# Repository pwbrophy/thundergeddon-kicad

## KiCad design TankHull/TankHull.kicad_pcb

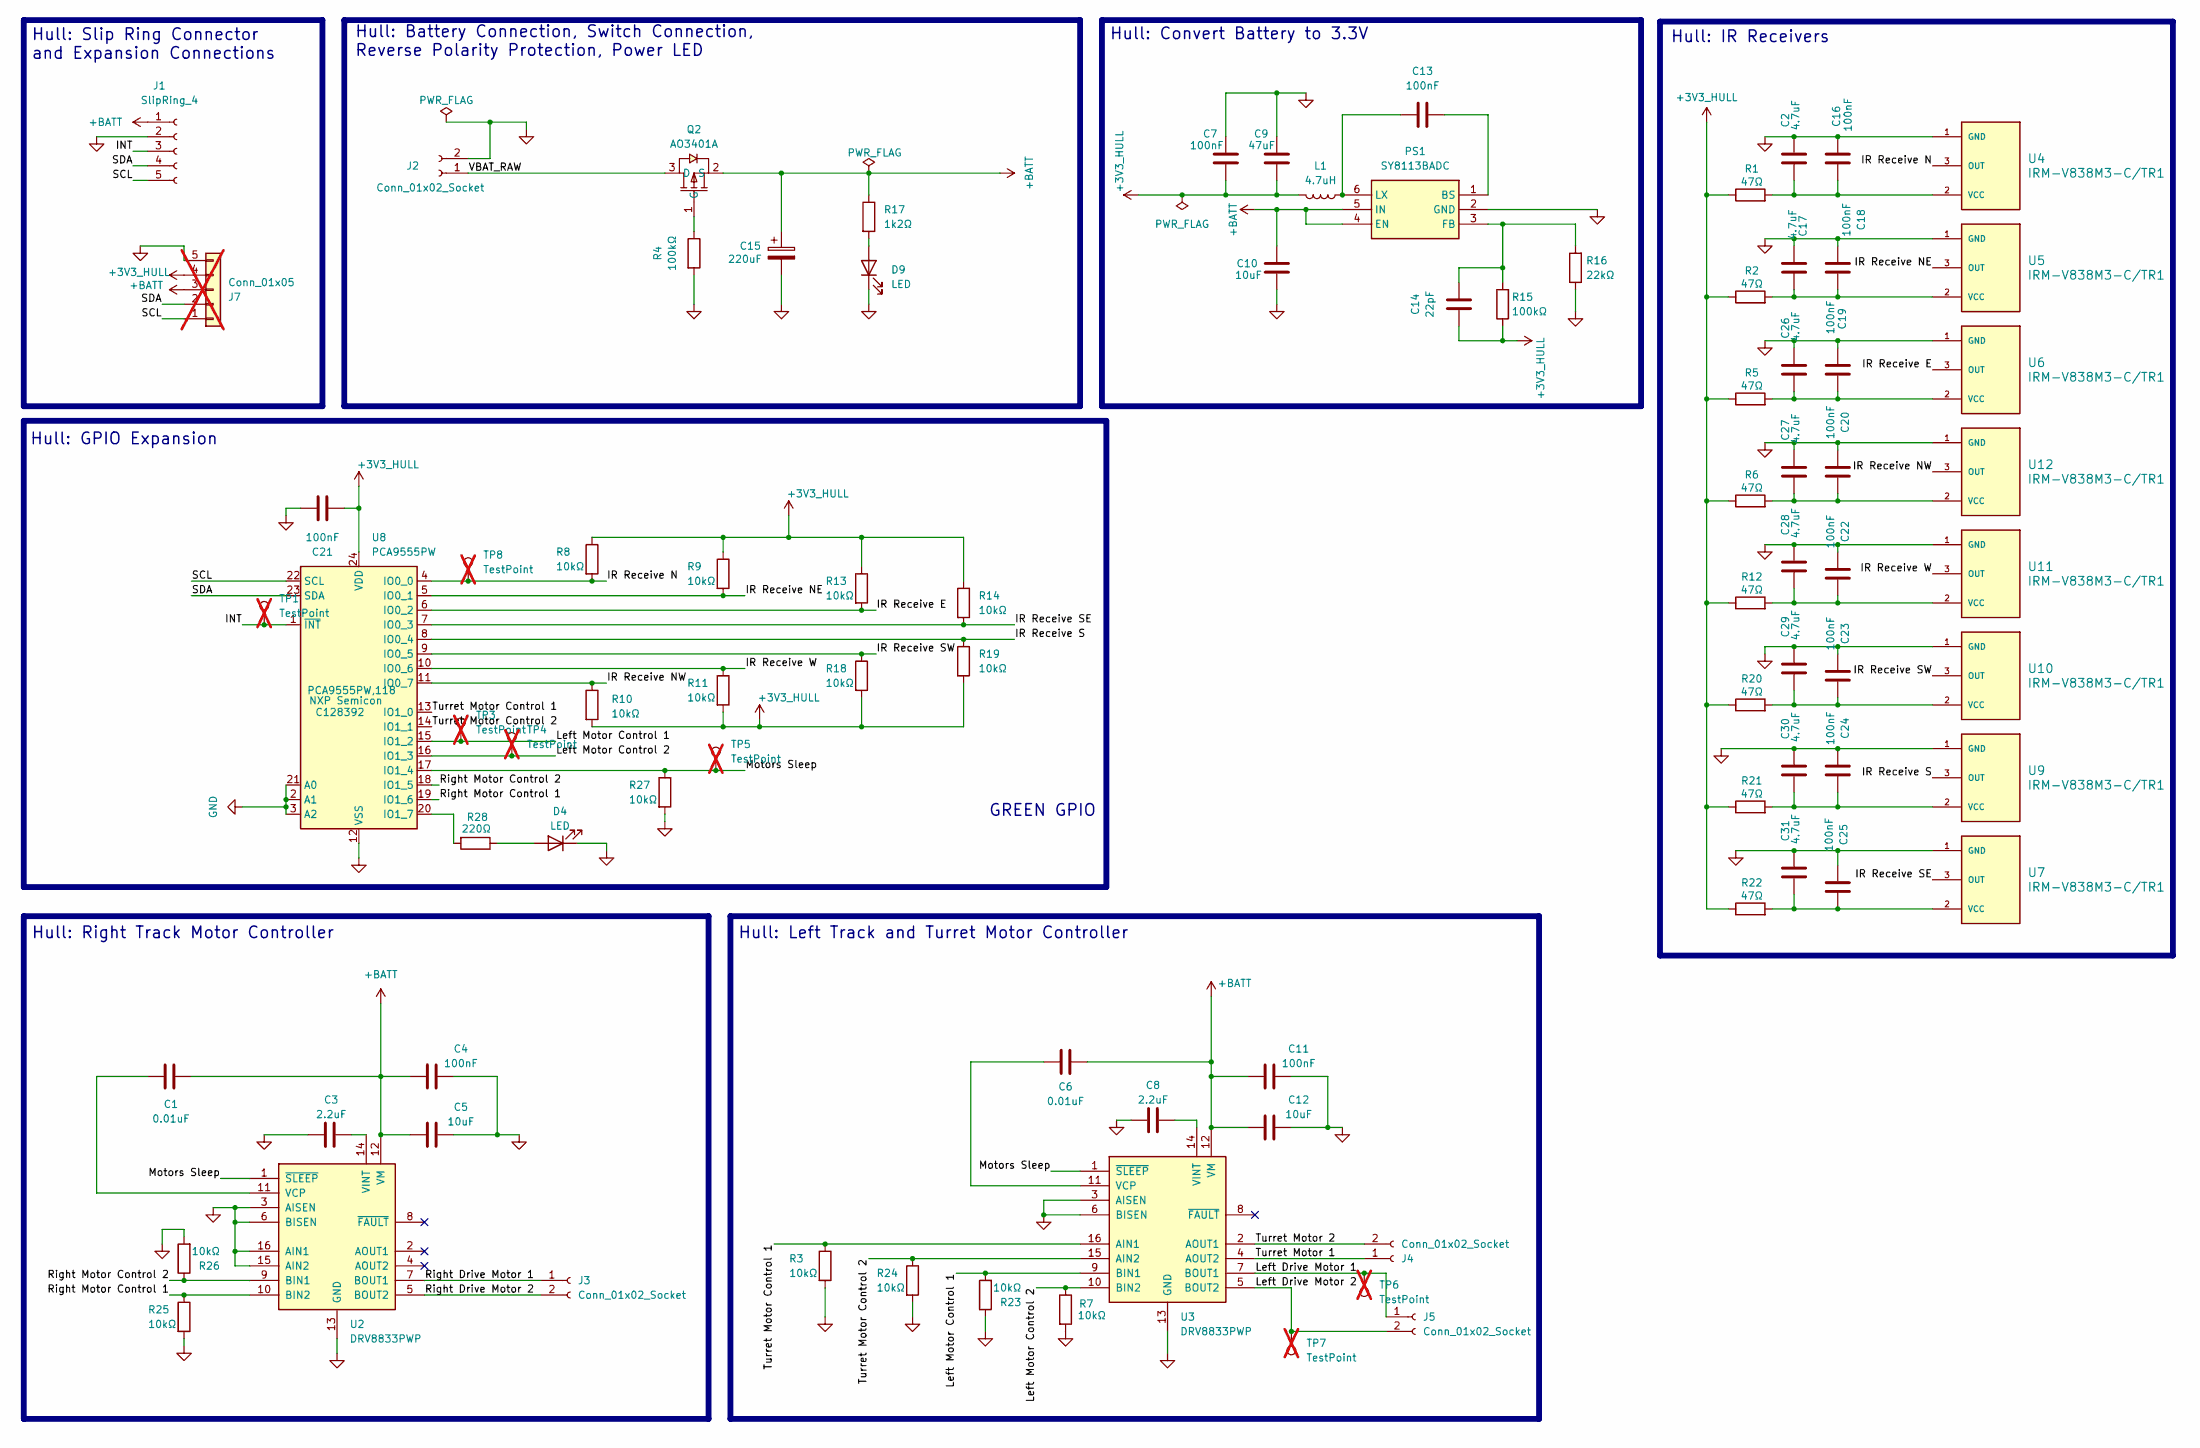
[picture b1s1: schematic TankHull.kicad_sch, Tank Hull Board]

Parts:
C1, C6: 0.01uF; C_0603_1608Metric; Manufacturer_Part_Number 0603B103K500NT; JLCPCB Part # C57112
C2, C17, C26, C27, C28, C29, C30, C31: 4.7uF; C_0805_2012Metric; JLCPCB Part # C1779
C3, C8: 2.2uF; C_0603_1608Metric; Manufacturer_Part_Number CL10A225KO8NNNC; JLCPCB Part # C23630
C4, C7, C11, C13, C16, C18, C19, C20, C21, C22, C23, C24, C25: 100nF; C_0603_1608Metric; Manufacturer_Part_Number CC0603KRX7R9BB104; JLCPCB Part # C14663
C5, C10, C12: 10uF; C_0805_2012Metric; Manufacturer_Part_Number CL21A106KAYNNNE; JLCPCB Part # C15850
C9: 47uF; C_0805_2012Metric; Manufacturer_Part_Number C16780; JLCPCB Part # C16780
C14: 22pF; C_0603_1608Metric; Manufacturer_Part_Number CL10C220JB8NNNC; JLCPCB Part # C1653
C15: 220uF; CP_Elec_6.3x7.7; Manufacturer_Part_Number RVT220UF16V67RV0015; JLCPCB Part # C2887273
D4: LED; LED_0805_2012Metric; JLCPCB Part # C2297
D9: LED; D_0603_1608Metric; Manufacturer_Part_Number KT-0603R; JLCPCB Part # C2286
J1: SlipRing_4; JST_PH_B5B-PH-K_1x05_P2.00mm_Vertical; JLCPCB Part # C157993
J2: Conn_01x02_Socket; JST_XH_B2B-XH-A_1x02_P2.50mm_Vertical; Manufacturer_Part_Number B2B-XH-A(LF)(SN); JLCPCB Part # C158012
J3, J4, J5: Conn_01x02_Socket; JST_PH_B2B-PH-K_1x02_P2.00mm_Vertical; Manufacturer_Part_Number B2B-PH-K-S(LF)(SN); JLCPCB Part # C131337
J7: Conn_01x05; PinSocket_1x05_P2.54mm_Vertical; Manufacturer_Part_Number 2.54-1*5PFemale; JLCPCB Part # C50950; not fitted
L1: 4.7uH; L_Changjiang_FXL0630; Manufacturer_Part_Number FXL0630-4R7-M; JLCPCB Part # C167220
PS1: SY8113BADC; SOT95P285X100-6N; Manufacturer_Part_Number SY8113BADC; JLCPCB Part # C78989
Q2: AO3401A; SOT-23_L2.9-W1.3-P1.90-LS2.4-BR; JLCPCB Part # C15127
R1, R2, R5, R6, R12, R20, R21, R22: 47Ω; R_0603_1608Metric; JLCPCB Part # C23182
R3, R7, R8, R9, R10, R11, R13, R14, R18, R19, R23, R24, R25, R26, R27: 10kΩ; R_0603_1608Metric; Manufacturer_Part_Number 0603WAF1002T5E; JLCPCB Part # C25804
R4, R15: 100kΩ; R_0603_1608Metric; Manufacturer_Part_Number 0603WAF1003T5E; JLCPCB Part # C25803
R16: 22kΩ; R_0603_1608Metric; Manufacturer_Part_Number 0603WAF2202T5E; JLCPCB Part # C31850
R17: 1k2Ω; R_0603_1608Metric; Manufacturer_Part_Number 0603WAF1201T5E; JLCPCB Part # C22765
R28: 220Ω; R_0603_1608Metric; JLCPCB Part # C22962
TP1, TP3, TP4, TP5, TP6, TP7, TP8: TestPoint; TestPoint_Pad_D1.0mm; not fitted
U2, U3: DRV8833PWP; HTSSOP-16-1EP_4.4x5mm_P0.65mm_EP3.4x5mm_Mask2.46x2.31mm_The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; Manufacturer_Part_Number DRV8833PWPR; JLCPCB Part # C50506
U4, U5, U6, U7, U9, U10, U11, U12: IRM-V838M3-C/TR1; XDCR_IRM-V838M3_TR1; PARTREV 7; JLCPCB Part # C3291489
U8: PCA9555PW; TSSOP-24_4.4x7.8mm_P0.65mm; Manufacturer_Part_Number PCA9555PW,118; JLCPCB Part # C128392

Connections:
+3V3_HULL: C7.1, C9.1, C14.2, C21.2, J7.4, L1.2, R1.1, R2.1, R5.1, R6.1, R8.1, R9.1, R10.2, R11.2, R12.1, R13.1, R14.1, R15.1, R18.2, R19.2, R20.1, R21.1, R22.1, U8.24 (VDD)
+BATT: C1.1, C4.2, C5.2, C6.1, C10.2, C11.2, C12.2, C15.1, J1.1, J7.3, PS1.4 (EN), PS1.5 (IN), Q2.2 (S), R17.1, U2.12 (VM), U3.12 (VM)
/INT: J1.3, TP1.1, U8.1 (~INT)
/IR Receive E: R13.2, U6.3 (OUT), U8.6 (IO0_2)
/IR Receive N: R8.2, TP8.1, U4.3 (OUT), U8.4 (IO0_0)
/IR Receive NE: R9.2, U5.3 (OUT), U8.5 (IO0_1)
/IR Receive NW: R10.1, U8.11 (IO0_7), U12.3 (OUT)
/IR Receive S: R19.1, U8.8 (IO0_4), U9.3 (OUT)
/IR Receive SE: R14.2, U7.3 (OUT), U8.7 (IO0_3)
/IR Receive SW: R18.1, U8.9 (IO0_5), U10.3 (OUT)
/IR Receive W: R11.1, U8.10 (IO0_6), U11.3 (OUT)
/Left Drive Motor 1: J5.1, TP6.1, U3.7 (BOUT1)
/Left Drive Motor 2: J5.2, TP7.1, U3.5 (BOUT2)
/Left Motor Control 1: R23.2, TP3.1, U3.9 (BIN1), U8.15 (IO1_2)
/Left Motor Control 2: R7.1, TP4.1, U3.10 (BIN2), U8.16 (IO1_3)
/Motors Sleep: R27.1, TP5.1, U2.1 (~SLEEP), U3.1 (~SLEEP), U8.17 (IO1_4)
/Right Drive Motor 1: J3.1, U2.7 (BOUT1)
/Right Drive Motor 2: J3.2, U2.5 (BOUT2)
/Right Motor Control 1: R25.1, U2.10 (BIN2), U8.19 (IO1_6)
/Right Motor Control 2: R26.1, U2.9 (BIN1), U8.18 (IO1_5)
/SCL: J1.5, J7.1, U8.22 (SCL)
/SDA: J1.4, J7.2, U8.23 (SDA)
/Turret Motor 1: J4.1, U3.4 (AOUT2)
/Turret Motor 2: J4.2, U3.2 (AOUT1)
/Turret Motor Control 1: R3.1, U3.16 (AIN1), U8.13 (IO1_0)
/Turret Motor Control 2: R24.1, U3.15 (AIN2), U8.14 (IO1_1)
/VBAT_RAW: J2.1, Q2.3 (D)
GND: C2.1, C3.1, C4.1, C5.1, C7.2, C8.1, C9.2, C10.1, C11.1, C12.1, C15.2, C16.1, C17.1, C18.1, C19.1, C20.1, C21.1, C22.1, C23.1, C24.1, C25.1, C26.1, C27.1, C28.1, C29.1, C30.1, C31.1, D4.1 (K), D9.1 (K), J1.2, J2.2, J7.5, PS1.2 (GND), R3.2, R4.2, R7.2, R16.1, R23.1, R24.2, R25.2, R26.2, R27.2, U2.3 (AISEN), U2.6 (BISEN), U2.13 (GND), U2.15 (AIN2), U2.16 (AIN1), U2.17 (GND), U3.3 (AISEN), U3.6 (BISEN), U3.13 (GND), U3.17 (GND), U4.1 (GND), U4.4 (GND), U5.1 (GND), U5.4 (GND), U6.1 (GND), U6.4 (GND), U7.1 (GND), U7.4 (GND), U8.2 (A1), U8.3 (A2), U8.12 (VSS), U8.21 (A0), U9.1 (GND), U9.4 (GND), U10.1 (GND), U10.4 (GND), U11.1 (GND), U11.4 (GND), U12.1 (GND), U12.4 (GND)
unnamed: D4.2 (A), R28.1
unnamed: D9.2 (A), R17.2
unnamed: C13.1, PS1.1 (BS)
unnamed: C14.1, PS1.3 (FB), R15.2, R16.2
unnamed: C13.2, L1.1, PS1.6 (LX)
unnamed: Q2.1 (G), R4.1
unnamed: C1.2, U2.11 (VCP)
unnamed: C3.2, U2.14 (VINT)
unnamed: C6.2, U3.11 (VCP)
unnamed: C8.2, U3.14 (VINT)
unnamed: C2.2, C16.2, R1.2, U4.2 (VCC)
unnamed: C17.2, C18.2, R2.2, U5.2 (VCC)
unnamed: C19.2, C26.2, R5.2, U6.2 (VCC)
unnamed: C25.2, C31.2, R22.2, U7.2 (VCC)
unnamed: R28.2, U8.20 (IO1_7)
unnamed: C24.2, C30.2, R21.2, U9.2 (VCC)
unnamed: C23.2, C29.2, R20.2, U10.2 (VCC)
unnamed: C22.2, C28.2, R12.2, U11.2 (VCC)
unnamed: C20.2, C27.2, R6.2, U12.2 (VCC)

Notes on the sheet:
GREEN GPIO
Hull: Left Track and Turret Motor Controller
Hull: Convert Battery to 3.3V
Hull: Slip Ring Connector and Expansion Connections
Hull: IR Receivers
Hull: Battery Connection, Switch Connection, Reverse Polarity Protection, Power LED
Hull: GPIO Expansion
Hull: Right Track Motor Controller

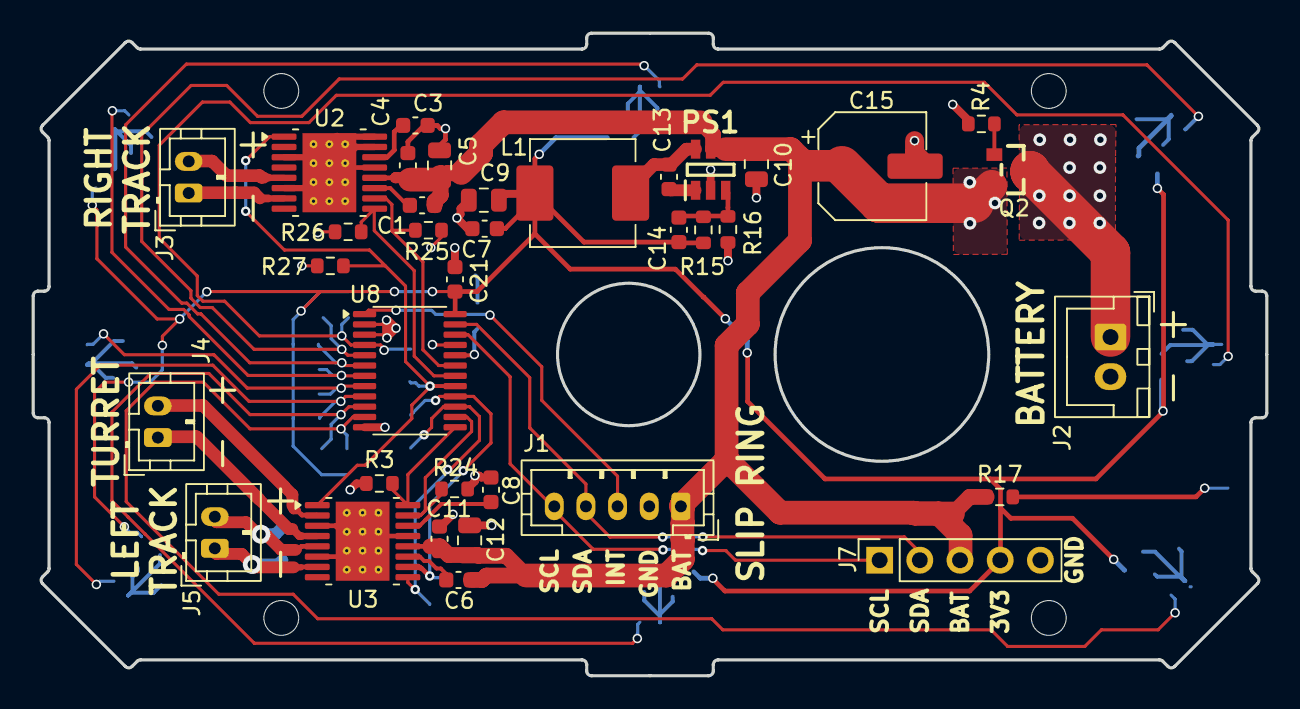
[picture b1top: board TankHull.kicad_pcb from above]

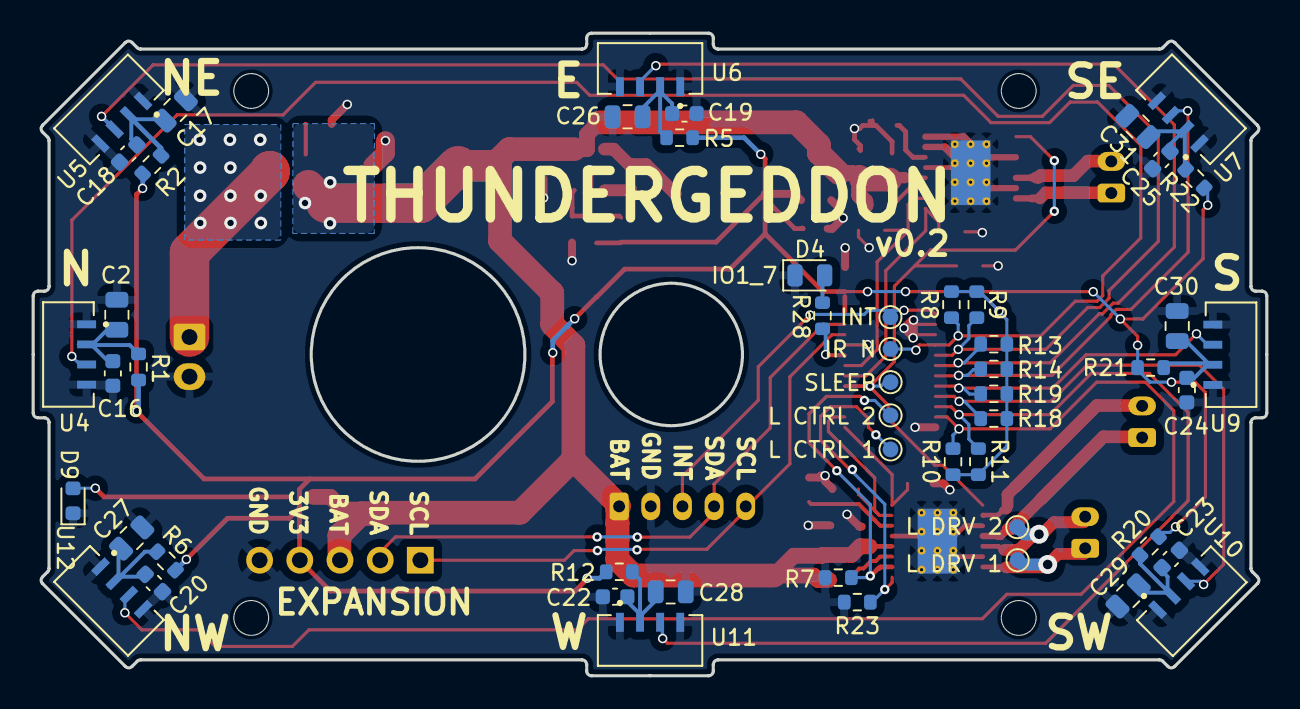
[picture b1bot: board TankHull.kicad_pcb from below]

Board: 2 copper layers, 77.9 x 40.6 mm, 88 parts (52 on the bottom side), 47 nets.

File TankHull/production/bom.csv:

Designator,Footprint,Quantity,Value,LCSC Part #
"C1, C6",0603,2,0.01uF,C57112
"C10, C12, C5",0805,3,10uF,C15850
"C11, C13, C16, C18, C19, C20, C21, C22, C23, C24, C25, C4, C7",0603,13,100nF,C14663
C14,0603,1,22pF,C1653
C15,CP_Elec_6.3x7.7,1,220uF,C2887273
"C17, C2, C26, C27, C28, C29, C30, C31",0805,8,4.7uF,C1779
"C3, C8",0603,2,2.2uF,C23630
C9,0805,1,47uF,C16780
D4,0805,1,LED,C2297
D9,0603,1,LED,C2286
J1,JST_PH_B5B-PH-K_1x05_P2.00mm_Vertical,1,SlipRing_4,C157993
J2,JST_XH_B2B-XH-A_1x02_P2.50mm_Vertical,1,Conn_01x02_Socket,C158012
"J3, J4, J5",JST_PH_B2B-PH-K_1x02_P2.00mm_Vertical,3,Conn_01x02_Socket,C131337
L1,L_Changjiang_FXL0630,1,4.7uH,C167220
PS1,SOT95P285X100-6N,1,SY8113BADC,C78989
Q2,SOT-23_L2.9-W1.3-P1.90-LS2.4-BR,1,AO3401A,C15127
"R1, R12, R2, R20, R21, R22, R5, R6",0603,8,47Ω,C23182
"R10, R11, R13, R14, R18, R19, R23, R24, R25, R26, R27, R3, R7, R8, R9",0603,15,10kΩ,C25804
"R15, R4",0603,2,100kΩ,C25803
R16,0603,1,22kΩ,C31850
R17,0603,1,1k2Ω,C22765
R28,0603,1,220Ω,C22962
"U10, U11, U12, U4, U5, U6, U7, U9",XDCR_IRM-V838M3_TR1,8,IRM-V838M3-C/TR1,C3291489
"U2, U3",HTSSOP-16-1EP_4.4x5mm_P0.65mm_EP3.4x5mm_Mask2.46x2.31mm_ThermalVias,2,DRV8833PWP,C50506
U8,TSSOP-24_4.4x7.8mm_P0.65mm,1,PCA9555PW,C128392

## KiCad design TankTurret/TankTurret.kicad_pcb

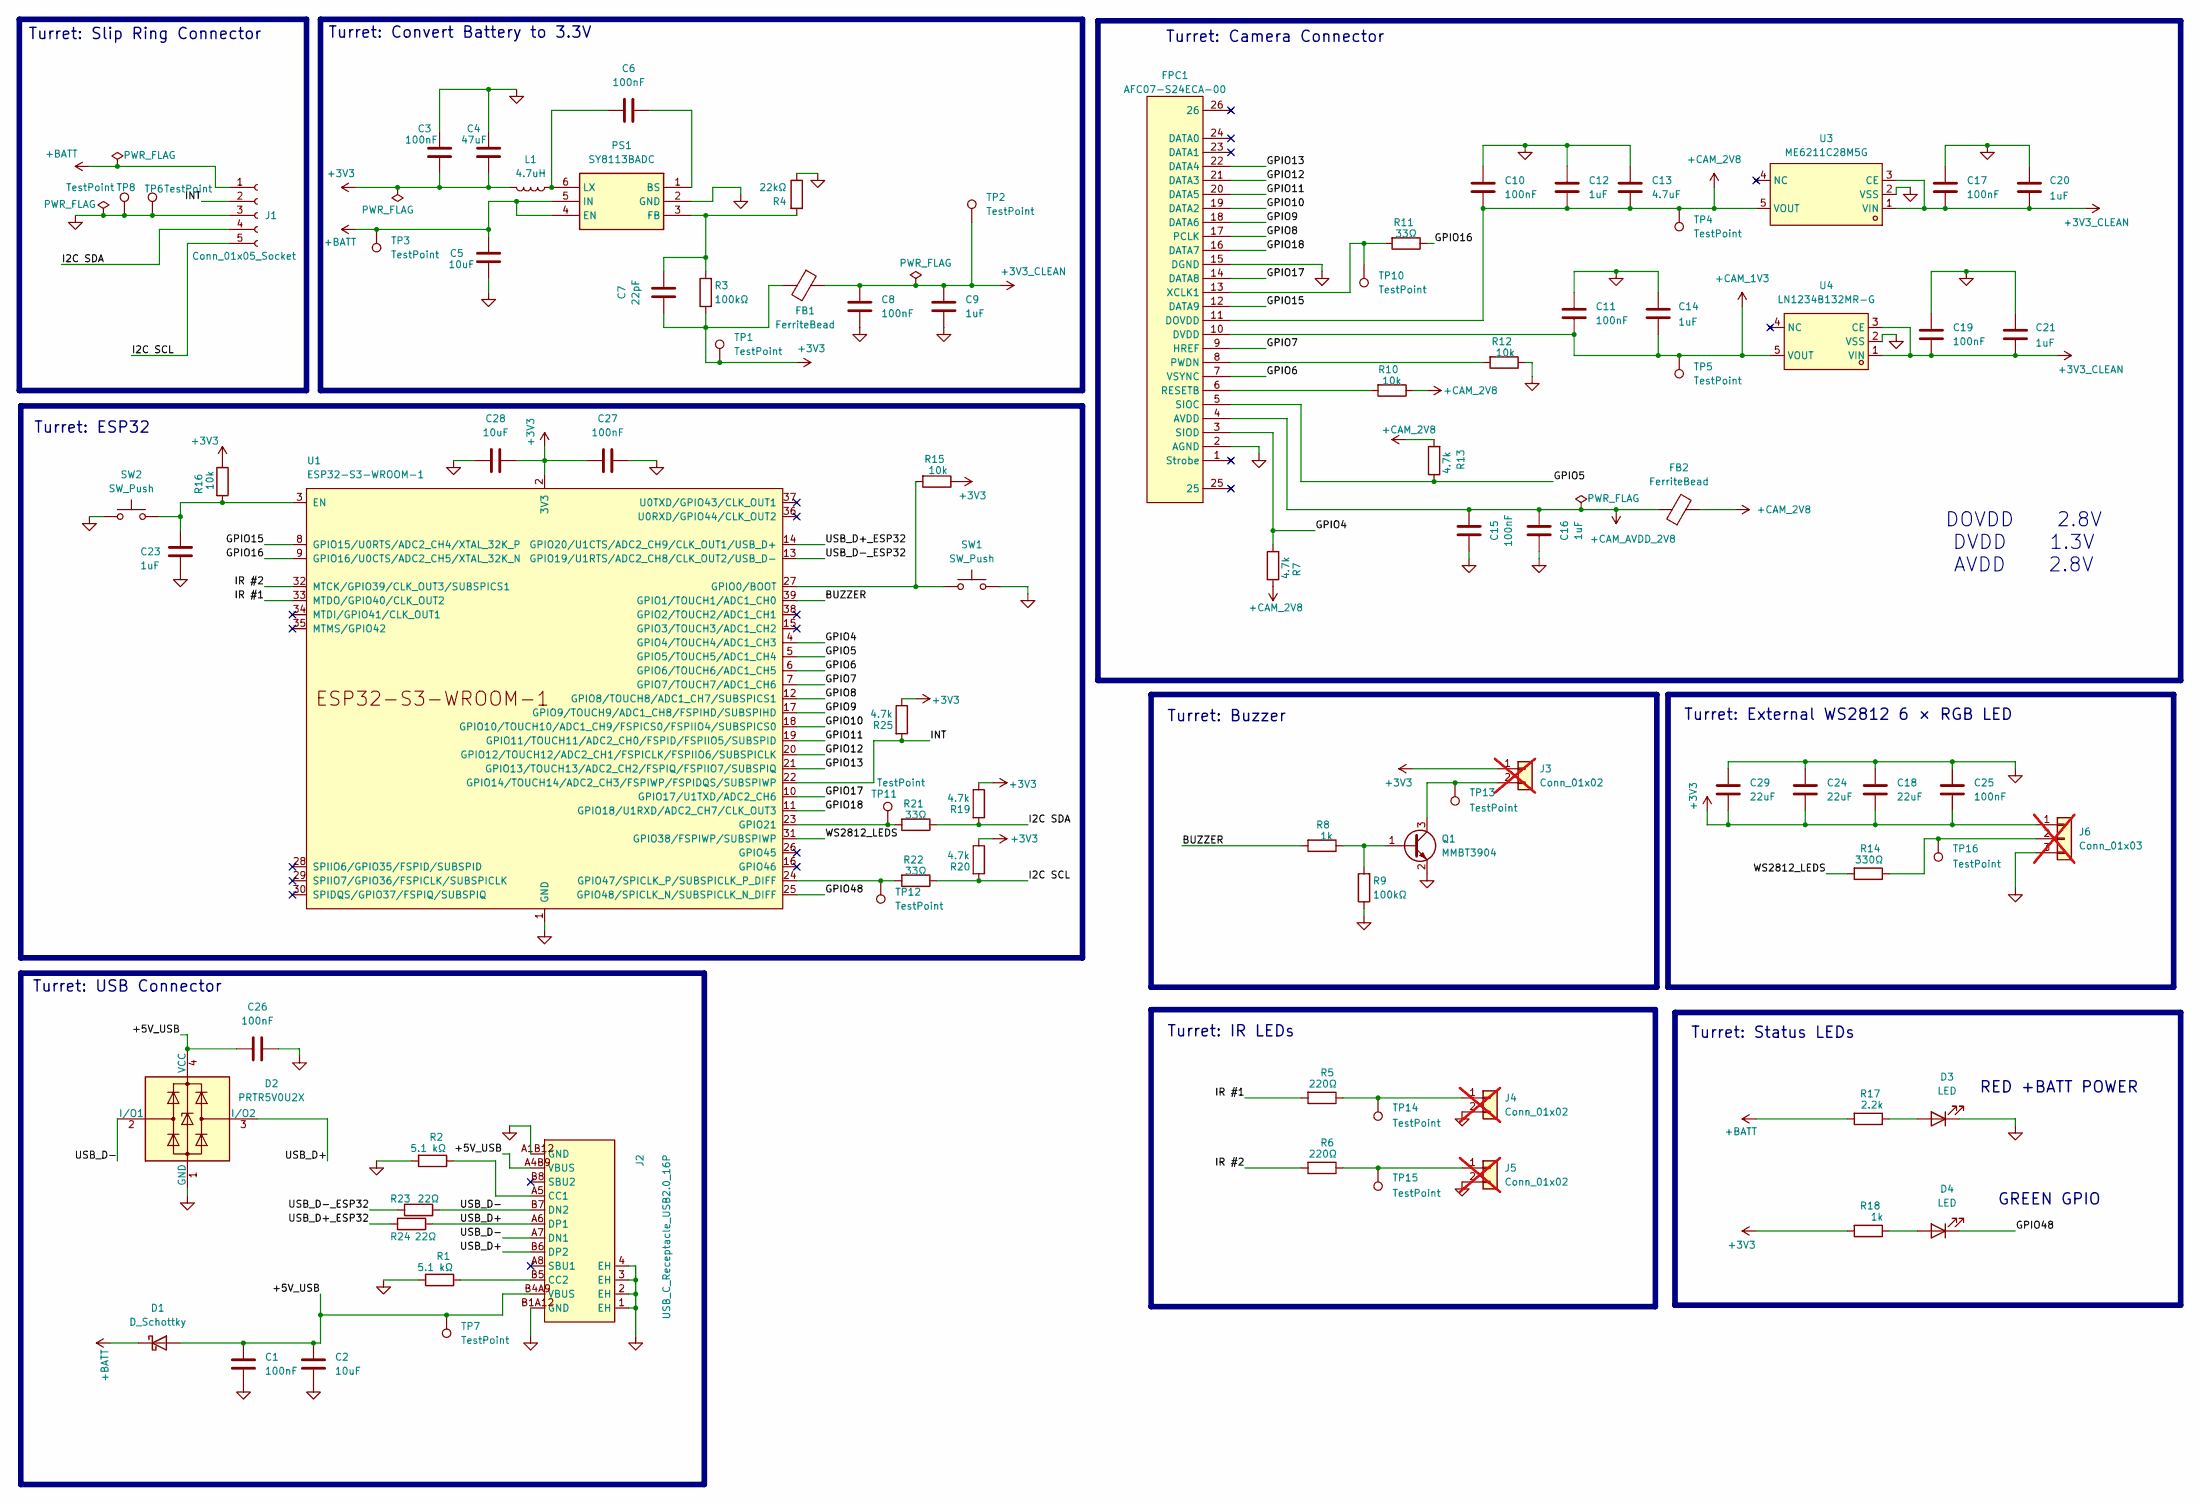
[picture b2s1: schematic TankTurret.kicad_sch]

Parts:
C1, C8, C15, C25, C26, C27: 100nF; C_0603_1608Metric; JLCPCB Part # C14663
C2, C28: 10uF; C_0805_2012Metric; JLCPCB Part # C15850
C3, C6: 100nF; C_0603_1608Metric; Manufacturer_Part_Number CC0603KRX7R9BB104; JLCPCB Part # C14663
C4: 47uF; C_0805_2012Metric; Manufacturer_Part_Number C16780; JLCPCB Part # C16780
C5: 10uF; C_0805_2012Metric; Manufacturer_Part_Number CL21A106KAYNNNE; JLCPCB Part # C15850
C7: 22pF; C_0603_1608Metric; Manufacturer_Part_Number CL10C220JB8NNNC; JLCPCB Part # C1653
C9, C12, C14, C16, C20, C21, C23: 1uF; C_0603_1608Metric; JLCPCB Part # C15849
C10, C11, C17, C19: 100nF; C_0402_1005Metric; JLCPCB Part # C1525
C13: 4.7uF; C_0805_2012Metric; JLCPCB Part # C1779
C18, C24, C29: 22uF; C_0805_2012Metric; Manufacturer_Part_Number CL21A226MAQNNNE; JLCPCB Part # C45783
D1: D_Schottky; D_SOD-123; Manufacturer_Part_Number B5819W SL; JLCPCB Part # C8598
D2: PRTR5V0U2X; SOT-143; JLCPCB Part # C5180302
D3: LED; LED_0603_1608Metric; JLCPCB Part # C2286
D4: LED; LED_0805_2012Metric; JLCPCB Part # C2297
FB1, FB2: FerriteBead; L_0603_1608Metric; JLCPCB Part # C1002
FPC1: AFC07-S24ECA-00; FPC-SMD_AFC07-S24ECA-00; LCSC Part C262643
J1: Conn_01x05_Socket; JST_PH_S5B-PH-K_1x05_P2.00mm_Horizontal; JLCPCB Part # C157923
J2: USB_C_Receptacle_USB2.0_16P; USB-C_SMD-TYPE-C-31-M-12_1; Manufacturer_Part_Number TYPE-C-31-M-12; JLCPCB Part # C165948
J3, J4, J5: Conn_01x02; PinHeader_1x02_P2.54mm_Vertical; not fitted
J6: Conn_01x03; PinHeader_1x03_P2.54mm_Vertical; not fitted
L1: 4.7uH; L_Changjiang_FXL0630; Manufacturer_Part_Number FXL0630-4R7-M; JLCPCB Part # C167220
PS1: SY8113BADC; SOT95P285X100-6N; Manufacturer_Part_Number SY8113BADC; JLCPCB Part # C78989
Q1: MMBT3904; SOT-23; Manufacturer_Part_Number MMBT3904(RANGE:100-300); JLCPCB Part # C20526
R1, R2: 5.1 kΩ; R_0603_1608Metric; JLCPCB Part # C23186
R3, R9: 100kΩ; R_0603_1608Metric; Manufacturer_Part_Number 0603WAF1003T5E; JLCPCB Part # C25803
R4: 22kΩ; R_0603_1608Metric; Manufacturer_Part_Number 0603WAF2202T5E; JLCPCB Part # C31850
R5, R6: 220Ω; R_0603_1608Metric; JLCPCB Part # C22962
R7, R13, R19, R20, R25: 4.7k; R_0603_1608Metric; JLCPCB Part # C23162
R8, R18: 1k; R_0603_1608Metric; JLCPCB Part # C21190
R10, R12, R15, R16: 10k; R_0603_1608Metric; JLCPCB Part # C25804
R11: 33Ω; R_0603_1608Metric; JLCPCB Part # C23140
R14: 330Ω; R_0603_1608Metric; JLCPCB Part # C23138
R17: 2.2k; R_0603_1608Metric; JLCPCB Part # C4190
R21, R22: 33Ω; R_0402_1005Metric; JLCPCB Part # C25105
R23, R24: 22Ω; R_0402_1005Metric; JLCPCB Part # C25092
SW1, SW2: SW_Push; SW_Push_1P1T_XKB_TS-1187A; Manufacturer_Part_Number TS-1187A-B-A-B; JLCPCB Part # C318884
TP1, TP2, TP3, TP4, TP5, TP6, TP7, TP8, TP10, TP11, TP12, TP13, TP14, TP15, TP16: TestPoint; TestPoint_Pad_D1.0mm
U1: ESP32-S3-WROOM-1; ESP32-S3-WROOM-1U; Manufacturer_Part_Number ESP32-S3-WROOM-1U-N16R8; JLCPCB Part # C3013946
U3: ME6211C28M5G; SOT-23-5; Manufacturer_Part_Number ME6211C28M5G-N; LCSC Part C53099
U4: LN1234B132MR-G; SOT-23-5; Manufacturer_Part_Number LN1234B132MR-G; LCSC Part C3008051

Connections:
+3V3: C3.1, C4.1, C7.2, C18.2, C24.2, C25.2, C27.2, C28.2, C29.2, FB1.2, J3.1, J6.1, L1.2, R3.1, R15.1, R16.1, R18.2, R19.1, R20.1, R25.1, TP1.1, U1.2 (3V3)
+3V3_CLEAN: C8.1, C9.1, C17.2, C19.2, C20.2, C21.2, FB1.1, TP2.1, U3.1 (VIN), U3.3 (CE), U4.1 (VIN), U4.3 (CE)
+BATT: C5.2, D1.1 (K), J1.1, PS1.4 (EN), PS1.5 (IN), R17.2, TP3.1
+CAM_1V3: C11.2, C14.2, FPC1.10 (DVDD), TP5.1, U4.5 (VOUT)
+CAM_2V8: C10.2, C12.2, C13.2, FB2.2, FPC1.11 (DOVDD), R7.1, R10.1, R13.2, TP4.1, U3.5 (VOUT)
+CAM_AVDD_2V8: C15.1, C16.1, FB2.1, FPC1.4 (AVDD)
/+5V_USB: C1.1, C2.1, C26.2, D1.2 (A), D2.4 (VCC), J2.A4B9 (VBUS), J2.B4A9 (VBUS), TP7.1
/BUZZER: R8.2, U1.39 (GPIO1/TOUCH1/ADC1_CH0)
/GPIO4: FPC1.3 (SIOD), R7.2, U1.4 (GPIO4/TOUCH4/ADC1_CH3)
/GPIO5: FPC1.5 (SIOC), R13.1, U1.5 (GPIO5/TOUCH5/ADC1_CH4)
/GPIO6: FPC1.7 (VSYNC), U1.6 (GPIO6/TOUCH6/ADC1_CH5)
/GPIO7: FPC1.9 (HREF), U1.7 (GPIO7/TOUCH7/ADC1_CH6)
/GPIO8: FPC1.17 (PCLK), U1.12 (GPIO8/TOUCH8/ADC1_CH7/SUBSPICS1)
/GPIO9: FPC1.18 (DATA6), U1.17 (GPIO9/TOUCH9/ADC1_CH8/FSPIHD/SUBSPIHD)
/GPIO10: FPC1.19 (DATA2), U1.18 (GPIO10/TOUCH10/ADC1_CH9/FSPICS0/FSPIIO4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)
/GPIO11: FPC1.20 (DATA5), U1.19 (GPIO11/TOUCH11/ADC2_CH0/FSPID/FSPIIO5/S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)
/GPIO12: FPC1.21 (DATA3), U1.20 (GPIO12/TOUCH12/ADC2_CH1/FSPICLK/FSPIIO6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)
/GPIO13: FPC1.22 (DATA4), U1.21 (GPIO13/TOUCH13/ADC2_CH2/FSPIQ/FSPIIO7/S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)
/GPIO15: FPC1.12 (DATA9), U1.8 (GPIO15/U0RTS/ADC2_CH4/XTAL_32K_P)
/GPIO16: R11.1, U1.9 (GPIO16/U0CTS/ADC2_CH5/XTAL_32K_N)
/GPIO17: FPC1.14 (DATA8), U1.10 (GPIO17/U1TXD/ADC2_CH6)
/GPIO18: FPC1.16 (DATA7), U1.11 (GPIO18/U1RXD/ADC2_CH7/CLK_OUT3)
/GPIO48: D4.1 (K), U1.25 (GPIO48/SPICLK_N/SUBSPICLK_N_DIFF)
/I2C SCL: J1.5, R20.2, R22.1
/I2C SDA: J1.4, R19.2, R21.1
/INT: J1.2, R25.2, U1.22 (GPIO14/TOUCH14/ADC2_CH3/FSPIWP/FSPIDQS/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)
/IR #1: R5.2, U1.33 (MTDO/GPIO40/CLK_OUT2)
/IR #2: R6.2, U1.32 (MTCK/GPIO39/CLK_OUT3/SUBSPICS1)
/USB_D+: D2.3 (I/O2), J2.A6 (DP1), J2.B6 (DP2), R24.1
/USB_D+_ESP32: R24.2, U1.14 (GPIO20/U1CTS/ADC2_CH9/CLK_OUT1/USB_D+)
/USB_D-: D2.2 (I/O1), J2.A7 (DN1), J2.B7 (DN2), R23.2
/USB_D-_ESP32: R23.1, U1.13 (GPIO19/U1RTS/ADC2_CH8/CLK_OUT2/USB_D-)
/WS2812_LEDS: R14.2, U1.31 (GPIO38/FSPIWP/SUBSPIWP)
GND: C1.2, C2.2, C3.2, C4.2, C5.1, C8.2, C9.2, C10.1, C11.1, C12.1, C13.1, C14.1, C15.2, C16.2, C17.1, C18.1, C19.1, C20.1, C21.1, C23.1, C24.1, C25.1, C26.1, C27.1, C28.1, C29.1, D2.1 (GND), D3.1 (K), FPC1.2 (AGND), FPC1.15 (DGND), J1.3, J2.1 (EH), J2.2 (EH), J2.3 (EH), J2.4 (EH), J2.A1B12 (GND), J2.B1A12 (GND), J4.2, J5.2, J6.3, PS1.2 (GND), Q1.2 (E), R1.2, R2.2, R4.1, R9.1, R12.1, SW1.2, SW2.1, TP6.1, TP8.1, U1.1 (GND), U1.40 (GND), U1.41 (GND), U3.2 (VSS), U4.2 (VSS)
unnamed: D3.2 (A), R17.1
unnamed: D4.2 (A), R18.1
unnamed: FPC1.8 (PWDN), R12.2
unnamed: FPC1.6 (RESETB), R10.2
unnamed: FPC1.13 (XCLK1), R11.2, TP10.1
unnamed: J2.A5 (CC1), R2.1
unnamed: J2.B5 (CC2), R1.1
unnamed: J3.2, Q1.3 (C), TP13.1
unnamed: J4.1, R5.1, TP14.1
unnamed: J5.1, R6.1, TP15.1
unnamed: J6.2, R14.1, TP16.1
unnamed: C6.1, PS1.1 (BS)
unnamed: C7.1, PS1.3 (FB), R3.2, R4.2
unnamed: C6.2, L1.1, PS1.6 (LX)
unnamed: Q1.1 (B), R8.1, R9.2
unnamed: C23.2, R16.2, SW2.2, U1.3 (EN)
unnamed: R15.2, SW1.1, U1.27 (GPIO0/BOOT)
unnamed: R21.2, TP11.1, U1.23 (GPIO21)
unnamed: R22.2, TP12.1, U1.24 (GPIO47/SPICLK_P/SUBSPICLK_P_DIFF)

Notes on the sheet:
DOVDD 2.8V DVDD 1.3V AVDD 2.8V
Turret: USB Connector
Turret: IR LEDs
Turret: ESP32
Turret: Camera Connector
Turret: Slip Ring Connector
Turret: Convert Battery to 3.3V
Turret: Buzzer
RED +BATT POWER
Turret: Status LEDs
GREEN GPIO
Turret: External WS2812 6 × RGB LED

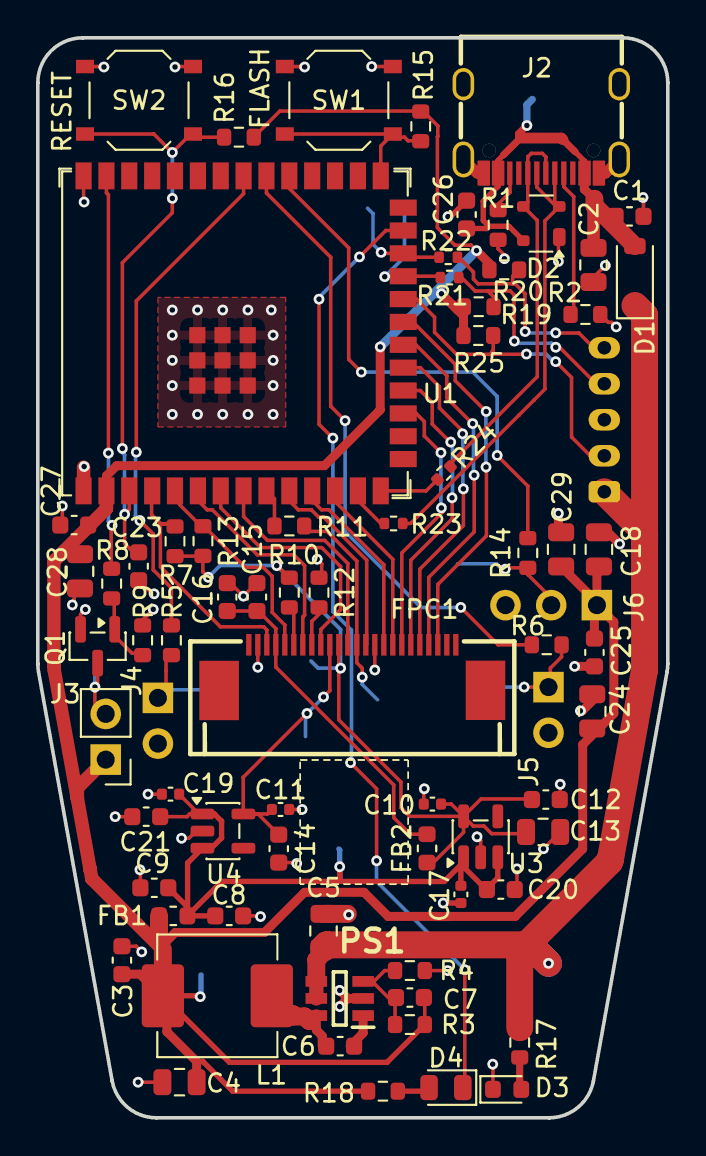
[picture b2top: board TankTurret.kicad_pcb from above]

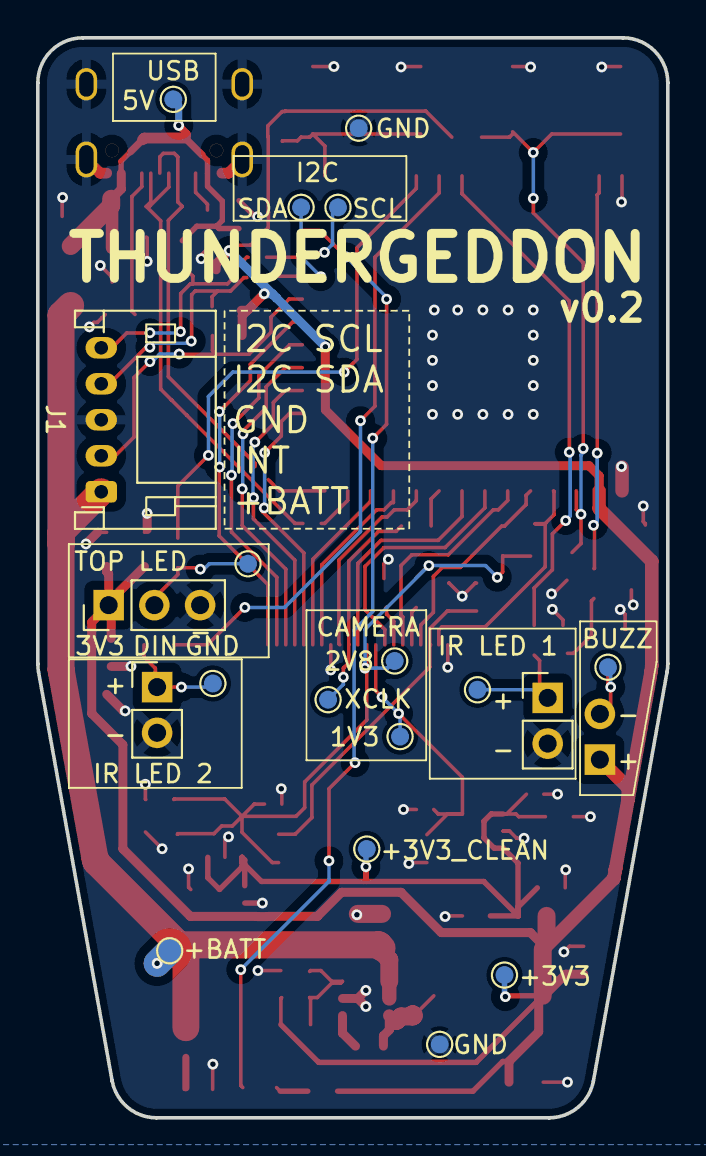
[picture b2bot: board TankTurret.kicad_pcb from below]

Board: 2 copper layers, 35.0 x 60.0 mm, 89 parts (19 on the bottom side), 53 nets.

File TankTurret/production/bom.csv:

Designator,Footprint,Quantity,Value,LCSC Part #
"C1, C15, C25, C26, C27, C3, C6, C8",0603,8,100nF,C14663
"C10, C11, C17, C19",0402,4,100nF,C1525
"C12, C14, C16, C20, C21, C23, C9",0603,7,1uF,C15849
C13,0805,1,4.7uF,C1779
"C18, C24, C29",0805,3,22uF,C45783
"C2, C28, C5",0805,3,10uF,C15850
C4,0805,1,47uF,C16780
C7,0603,1,22pF,C1653
D1,D_SOD-123,1,D_Schottky,C8598
D2,SOT-143,1,PRTR5V0U2X,C5180302
D3,0603,1,LED,C2286
D4,0805,1,LED,C2297
"FB1, FB2",0603,2,FerriteBead,C1002
FPC1,FPC-SMD_AFC07-S24ECA-00,1,AFC07-S24ECA-00,C262643
J1,JST_PH_S5B-PH-K_1x05_P2.00mm_Horizontal,1,Conn_01x05_Socket,C157923
J2,USB-C_SMD-TYPE-C-31-M-12_1,1,USB_C_Receptacle_USB2.0_16P,C165948
L1,L_Changjiang_FXL0630,1,4.7uH,C167220
PS1,SOT95P285X100-6N,1,SY8113BADC,C78989
Q1,SOT-23,1,MMBT3904,C20526
"R1, R2",0603,2,5.1 kΩ,C23186
"R10, R12, R15, R16",0603,4,10k,C25804
R11,0603,1,33Ω,C23140
"R13, R19, R20, R25, R7",0603,5,4.7k,C23162
R14,0603,1,330Ω,C23138
R17,0603,1,2.2k,C4190
"R18, R8",0603,2,1k,C21190
"R21, R22",0402,2,33Ω,C25105
"R23, R24",0402,2,22Ω,C25092
"R3, R9",0603,2,100kΩ,C25803
R4,0603,1,22kΩ,C31850
"R5, R6",0603,2,220Ω,C22962
"SW1, SW2",SW_Push_1P1T_XKB_TS-1187A,2,SW_Push,C318884
U1,ESP32-S3-WROOM-1U,1,ESP32-S3-WROOM-1,C3013946
U3,SOT-23-5,1,ME6211C28M5G,C53099
U4,SOT-23-5,1,LN1234B132MR-G,C3008051

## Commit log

2026-01-02 First upload!
2026-01-04 began IR receiver update on hull board
2026-01-05 continue with ir receiver update
2026-01-07 continued with IR receiver update
2026-01-09 submit before using cleanup tool
2026-01-11 tweaks
2026-01-16 camera connector
2026-01-19 bits
2026-03-15 V0.2 Files sent to JLC PCB on 15/03/2026
